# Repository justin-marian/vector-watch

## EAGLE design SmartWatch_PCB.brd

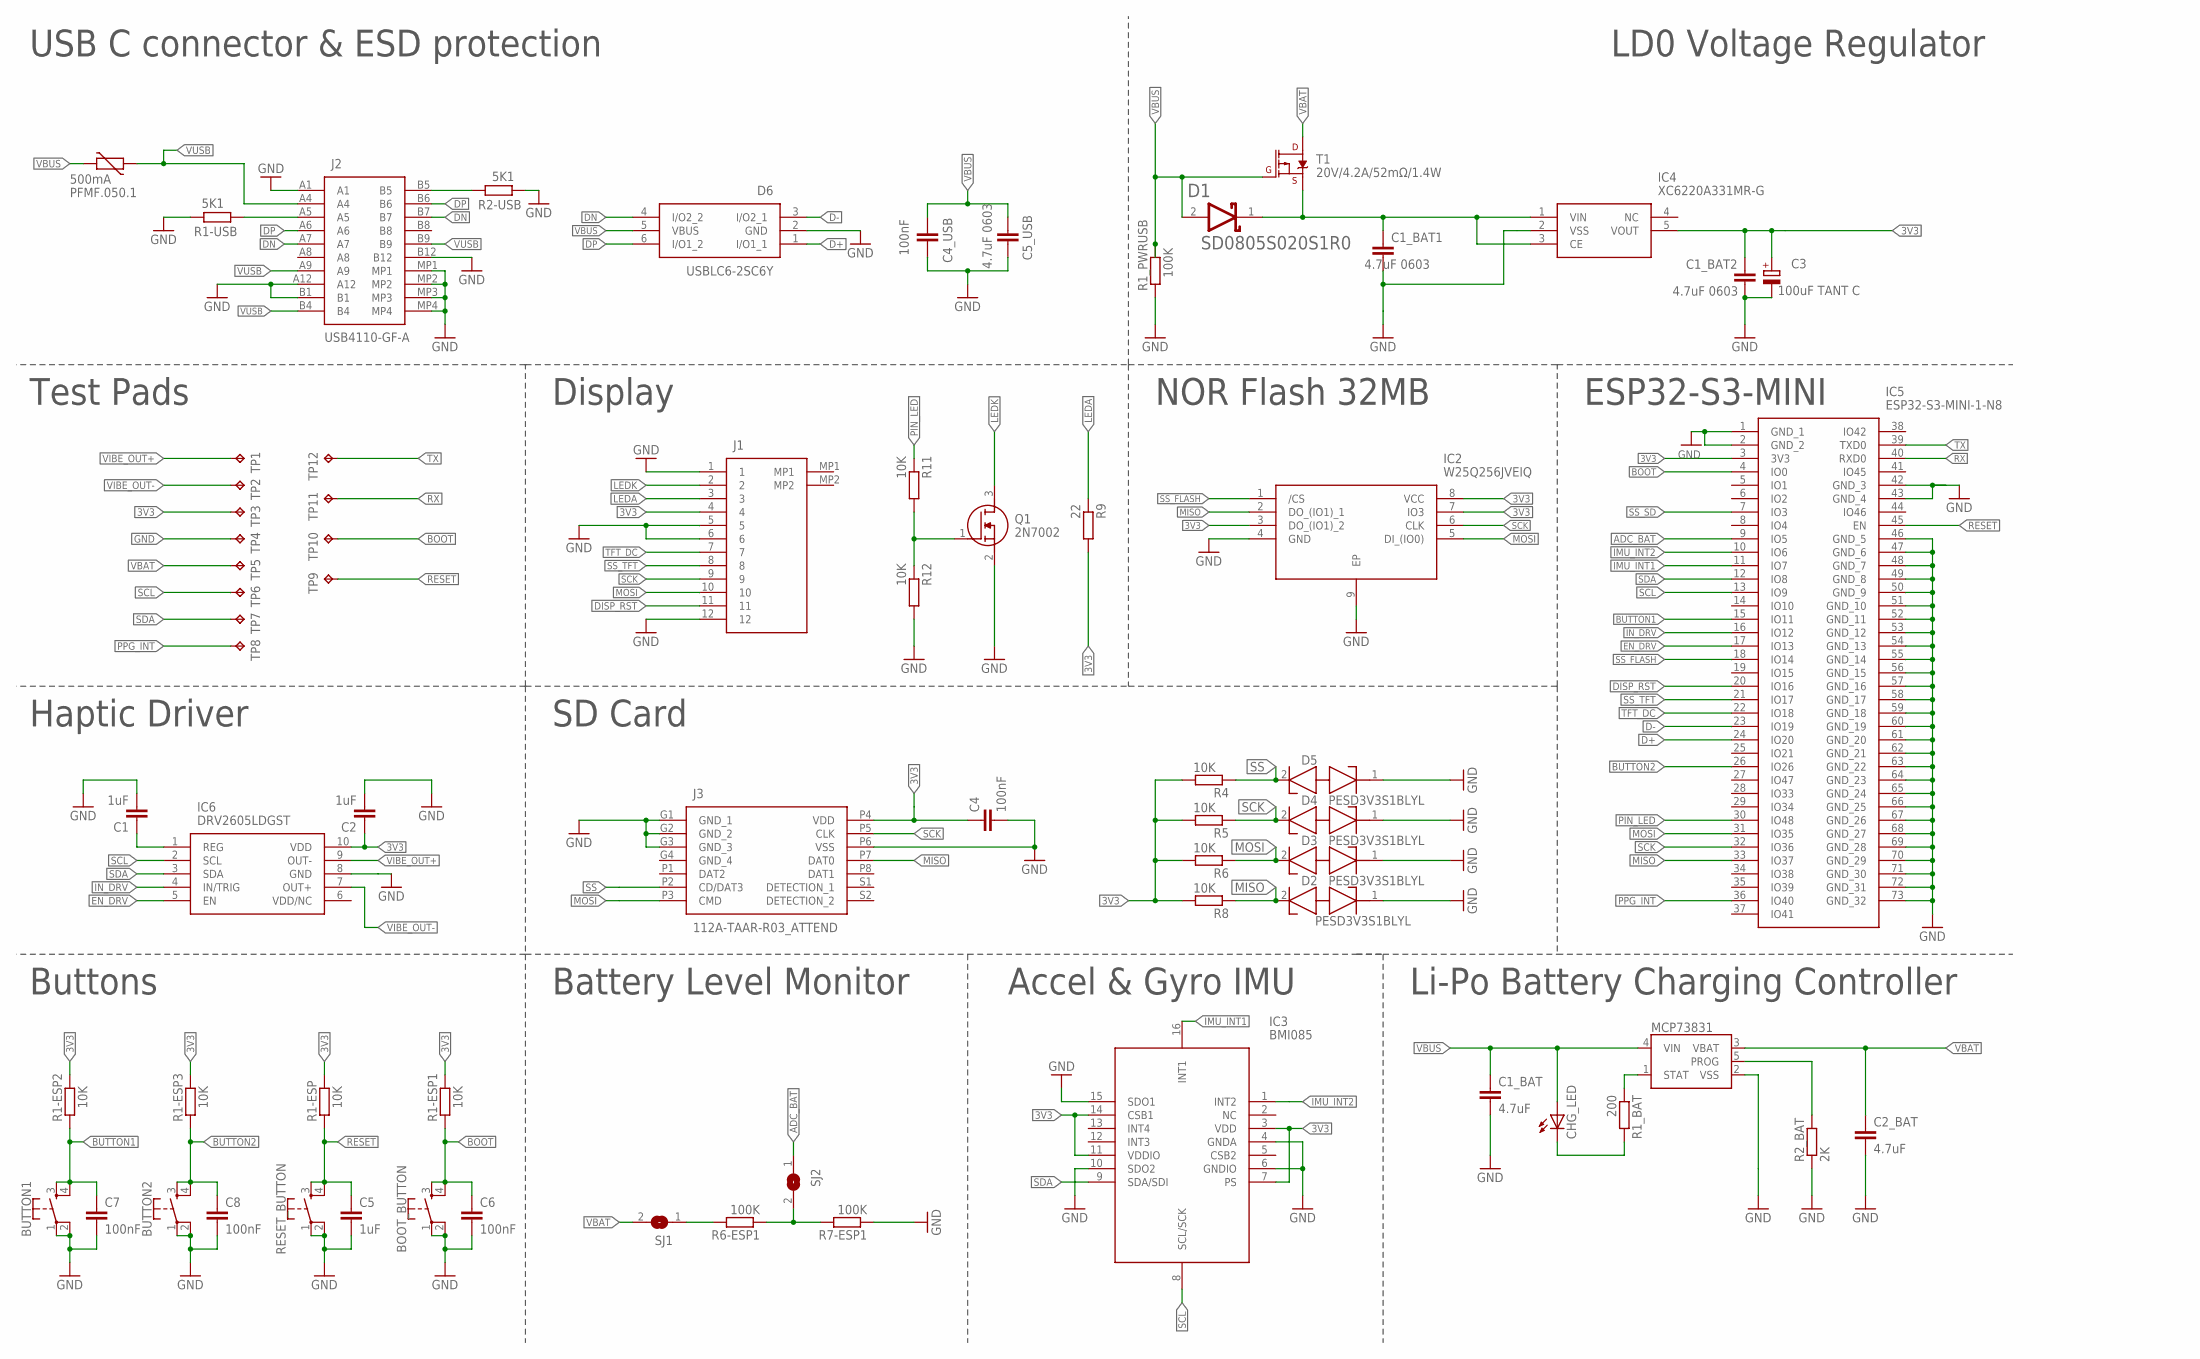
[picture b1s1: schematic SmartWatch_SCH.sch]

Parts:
BOOT_BUTTON: SPARKFUN-SWITCHES_MOMENTARY-SWITCH-SPST-2-SMD-4.6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; SPARKFUN-SWITCHES_TACTILE_SWITCH_SMD_4.6X2.8MM
BUTTON1, BUTTON2: SPARKFUN-SWITCHES_MOMENTARY-SWITCH-SPST-2-SMD-4.6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; SPARKFUN-SWITCHES_TACTILE_SWITCH_SMD_4.6X2.8MM
C1, C2, C5: 1uF; EAGLE-LTSPICE_C0402
C1_BAT: 4.7uF; EAGLE-LTSPICE_C0402
C1_BAT1, C1_BAT2, C5_USB: 4.7uF 0603; RCL_C0603
C2_BAT: 4.7uF; RCL_C0603
C3: 100uF TANT C; CT3528
C4, C4_USB, C6, C7, C8: 100nF; EAGLE-LTSPICE_C0402
CHG_LED: ADAFRUIT_LEDCHIP-LED0603; ADAFRUIT_CHIP-LED0603
D1: AVX---SD0805S020S1R0_AVX_SD0805S020S1R0AVX_SD0805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; AVX---SD0805S020S1R0_AVX_SD0805S020S1R0_0
D2, D3, D4, D5: PESD3V3S1BLYL; PESD5V0S1BL315
D6: USBLC6-2SC6Y; SOT95P280X145-6N
IC2: W25Q256JVEIQ; SON127P800X600X80-9N
IC3: BMI085
IC4: XC6220A331MR-G; SOT95P280X120-5N
IC5: ESP32-S3-MINI-1-N8; ESP32S3MINI1N8
IC6: DRV2605LDGST; SOP50P490X110-10N
J1: PCA-6-LA-12-HL-3-T_R; PCA6LA12HL3TR
J2: USB4110-GF-A; USB4110GFA
J3: 112A-TAAR-R03_ATTEND; 112ATAARR03ATTEND
MCP73831: SPARKFUN-IC-POWER_MCP73831; SPARKFUN-IC-POWER_SOT23-5
PFMF.050.1: 500mA; VARISTOR_CT/CN1812
Q1: 2N7002; SOT96P240X120-3N
R1-ESP, R1-ESP1, R1-ESP2, R1-ESP3, R4, R5, R6, R8, R11, R12: 10K; EAGLE-LTSPICE_R0402
R1-USB, R2-USB: 5K1; EAGLE-LTSPICE_R0402
R1_BAT: 200; EAGLE-LTSPICE_R0402
R1_PWRUSB, R6-ESP1, R7-ESP1: 100K; EAGLE-LTSPICE_R0402
R2_BAT: 2K; EAGLE-LTSPICE_R0402
R9: 22; EAGLE-LTSPICE_R0402
RESET_BUTTON: SPARKFUN-SWITCHES_MOMENTARY-SWITCH-SPST-2-SMD-4.6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; SPARKFUN-SWITCHES_TACTILE_SWITCH_SMD_4.6X2.8MM
SJ1, SJ2: SJ
T1: 20V/4.2A/52mΩ/1.4W; SPARKFUN-DISCRETESEMI_SOT23-3
TP1, TP2, TP3, TP4, TP5, TP6, TP7, TP8, TP9, TP10, TP11, TP12: TPTP20R; TP20R

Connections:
3V3: C1_BAT2.1, C2.1, C3.+, C4.1, IC2.3 (DO_(IO1)_2), IC2.7 (IO3), IC2.8 (VCC), IC3.3 (VDD), IC3.7 (PS), IC3.11 (VDDIO), IC3.14 (CSB1), IC4.5 (VOUT), IC5.3 (3V3), IC6.10 (VDD), J1.4, J3.P4 (VDD), R1-ESP.2, R1-ESP1.2, R1-ESP2.2, R1-ESP3.2, R4.2, R5.2, R6.2, R8.2, R9.1, TP3.TP
ADC_BAT: IC5.9 (IO5), SJ2.1
BOOT: BOOT_BUTTON.3, BOOT_BUTTON.4, C6.1, IC5.4 (IO0), R1-ESP1.1, TP10.TP
BUTTON1: BUTTON1.3, BUTTON1.4, C7.1, IC5.15 (IO11), R1-ESP2.1
BUTTON2: BUTTON2.3, BUTTON2.4, C8.1, IC5.26 (IO26), R1-ESP3.1
D+: D6.1 (I/O1_1), IC5.24 (IO20)
D-: D6.3 (I/O2_1), IC5.23 (IO19)
DISP_RST: IC5.20 (IO16), J1.11
DN: D6.4 (I/O2_2), J2.A7, J2.B7
DP: D6.6 (I/O1_2), J2.A6, J2.B6
EN_DRV: IC5.17 (IO13), IC6.5 (EN)
GND: BOOT_BUTTON.1, BOOT_BUTTON.2, BUTTON1.1, BUTTON1.2, BUTTON2.1, BUTTON2.2, C1.2, C1_BAT.2, C1_BAT1.2, C1_BAT2.2, C2.2, C2_BAT.2, C3.-, C4.2, C4_USB.2, C5.2, C5_USB.2, C6.2, C7.2, C8.2, D2.1 (K1), D3.1 (K1), D4.1 (K1), D5.1 (K1), D6.2 (GND), IC2.4 (GND), IC2.9 (EP), IC3.4 (GNDA), IC3.6 (GNDIO), IC3.10 (SDO2), IC3.15 (SDO1), IC4.2 (VSS), IC5.1 (GND_1), IC5.2 (GND_2), IC5.42 (GND_3), IC5.43 (GND_4), IC5.46 (GND_5), IC5.47 (GND_6), IC5.48 (GND_7), IC5.49 (GND_8), IC5.50 (GND_9), IC5.51 (GND_10), IC5.52 (GND_11), IC5.53 (GND_12), IC5.54 (GND_13), IC5.55 (GND_14), IC5.56 (GND_15), IC5.57 (GND_16), IC5.58 (GND_17), IC5.59 (GND_18), IC5.60 (GND_19), IC5.61 (GND_20), IC5.62 (GND_21), IC5.63 (GND_22), IC5.64 (GND_23), IC5.65 (GND_24), IC5.66 (GND_25), IC5.67 (GND_26), IC5.68 (GND_27), IC5.69 (GND_28), IC5.70 (GND_29), IC5.71 (GND_30), IC5.72 (GND_31), IC5.73 (GND_32), IC6.8 (GND), J1.1, J1.5, J1.6, J1.12, J2.A1, J2.A12, J2.B1, J2.B12, J2.MP1, J2.MP2, J2.MP3, J2.MP4, J3.G1 (GND_1), J3.G2 (GND_2), J3.G3 (GND_3), J3.P6 (VSS), MCP73831.2 (VSS), Q1.2 (S), R1-USB.2, R1_PWRUSB.1, R2-USB.1, R2_BAT.1, R7-ESP1.1, R12.1, RESET_BUTTON.1, RESET_BUTTON.2, TP4.TP
IMU_INT1: IC3.16 (INT1), IC5.11 (IO7)
IMU_INT2: IC3.1 (INT2), IC5.10 (IO6)
IN_DRV: IC5.16 (IO12), IC6.4 (IN/TRIG)
LEDA: J1.3, R9.2
LEDK: J1.2, Q1.3 (D)
MISO: D2.2 (K2), IC2.2 (DO_(IO1)_1), IC5.33 (IO37), J3.P7 (DAT0), R8.1
MOSI: D3.2 (K2), IC2.5 (DI_(IO0)), IC5.31 (IO35), J1.10, J3.P3 (CMD), R6.1
unnamed: Q1.1 (G), R11.1, R12.2
unnamed: C1_BAT1.1, D1.1 (CATHODE), IC4.1 (VIN), IC4.3 (CE), T1.2 (S)
unnamed: R6-ESP1.1, R7-ESP1.2, SJ2.2
unnamed: J2.A5, R1-USB.1
unnamed: R6-ESP1.2, SJ1.1
unnamed: J2.B5, R2-USB.2
unnamed: MCP73831.5 (PROG), R2_BAT.2
unnamed: MCP73831.1 (STAT), R1_BAT.1
unnamed: C1.1, IC6.1 (REG)
unnamed: CHG_LED.C, R1_BAT.2
PIN_LED: IC5.30 (IO48), R11.2
PPG_INT: IC5.36 (IO40), TP8.TP
RESET: C5.1, IC5.45 (EN), R1-ESP.1, RESET_BUTTON.3, RESET_BUTTON.4, TP9.TP
RX: IC5.40 (RXD0), TP11.TP
SCK: D4.2 (K2), IC2.6 (CLK), IC5.32 (IO36), J1.9, J3.P5 (CLK), R5.1
SCL: IC3.8 (SCL/SCK), IC5.13 (IO9), IC6.2 (SCL), TP6.TP
SDA: IC3.9 (SDA/SDI), IC5.12 (IO8), IC6.3 (SDA), TP7.TP
SS: D5.2 (K2), J3.P2 (CD/DAT3), R4.1
SS_FLASH: IC2.1 (/CS), IC5.18 (IO14)
SS_SD: IC5.7 (IO3)
SS_TFT: IC5.21 (IO17), J1.8
TFT_DC: IC5.22 (IO18), J1.7
TX: IC5.39 (TXD0), TP12.TP
VBAT: C2_BAT.1, MCP73831.3 (VBAT), SJ1.2, T1.3 (D), TP5.TP
VBUS: C1_BAT.1, C4_USB.1, C5_USB.1, CHG_LED.A, D1.2 (ANODE), D6.5 (VBUS), MCP73831.4 (VIN), PFMF.050.1.2, R1_PWRUSB.2, T1.1 (G)
VIBE_OUT+: IC6.9 (OUT-), TP1.TP
VIBE_OUT-: IC6.7 (OUT+), TP2.TP
VUSB: J2.A4, J2.A9, J2.B4, J2.B9, PFMF.050.1.1

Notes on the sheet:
LD0 Voltage Regulator
USB C connector & ESD protection
Test Pads
Display
NOR Flash 32MB
ESP32-S3-MINI
Haptic Driver
SD Card
Buttons
Battery Level Monitor
Accel & Gyro IMU
Li-Po Battery Charging Controller

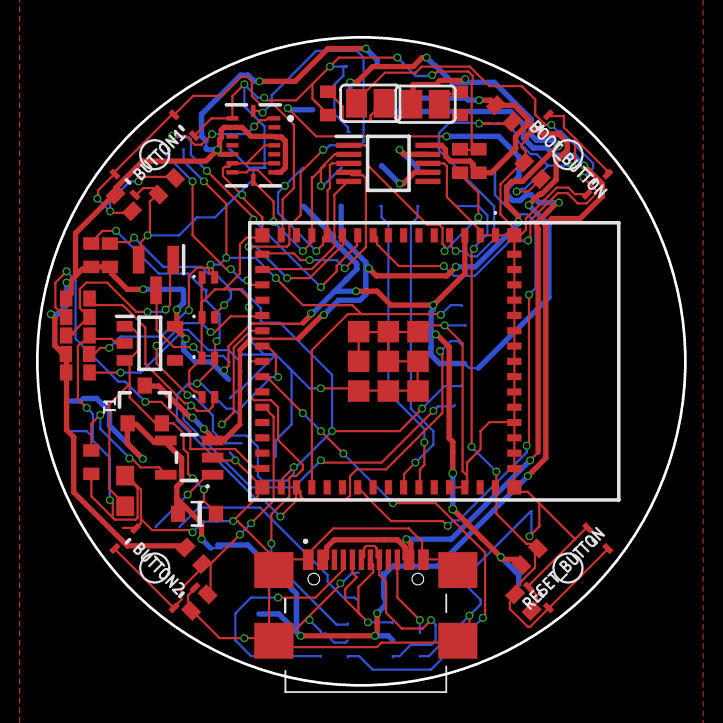
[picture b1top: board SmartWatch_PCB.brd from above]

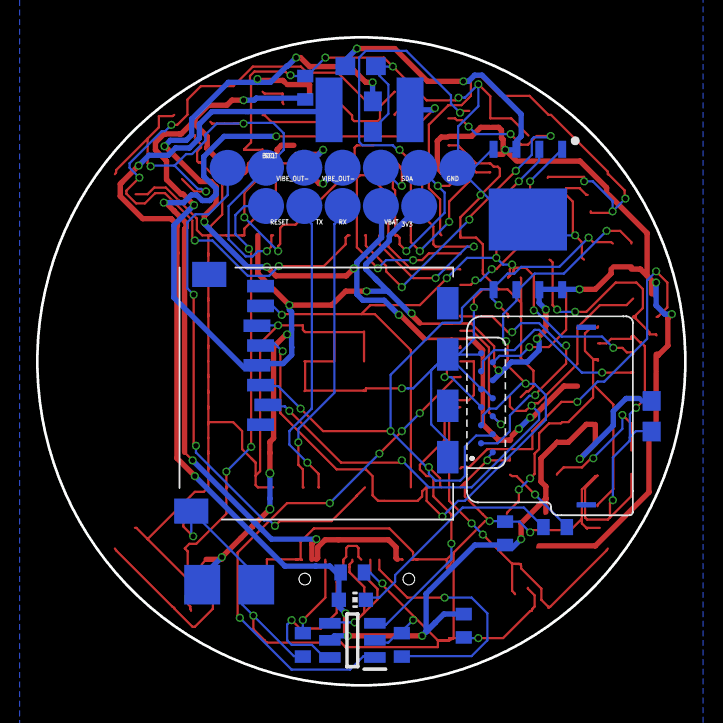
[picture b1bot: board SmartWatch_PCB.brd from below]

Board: 2 copper layers, 36.0 x 36.0 mm, 69 parts (29 on the bottom side), 46 nets.

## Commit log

2024-04-07 Footprint images TOP/BOTTOM Vector Watch.
2024-04-07 Added Schematic File.
2024-04-07 Added PCB Board file.
